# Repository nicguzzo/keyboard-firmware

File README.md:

firmware for 2 pieces ergonomic mechanical keyboard

pacman -S arm-none-eabi-gcc arm-none-eabi-gdb arm-none-eabi-binutils arm-none-eabi-newlib

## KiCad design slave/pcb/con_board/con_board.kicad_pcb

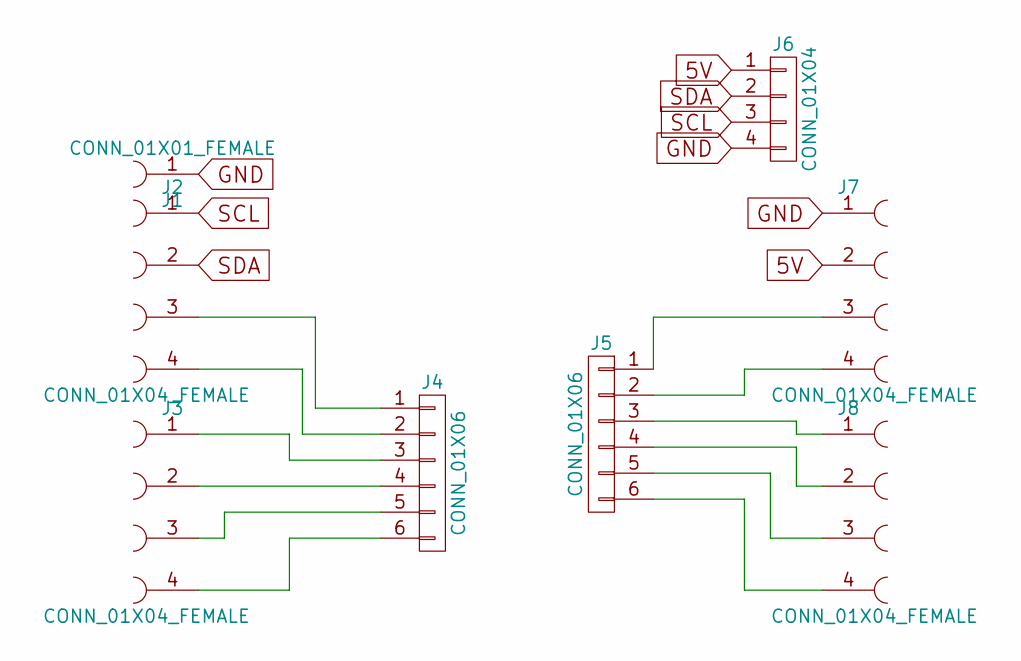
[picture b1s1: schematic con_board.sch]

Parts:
J1: CONN_01X01_FEMALE; Pin_Header_Straight_1x01_Pitch2.54mm
J2, J3, J7, J8: CONN_01X04_FEMALE; Pin_Header_Straight_1x04_Pitch2.54mm
J4, J5: CONN_01X06; Pin_Header_Straight_1x06_Pitch2.54mm
J6: CONN_01X04; Pin_Header_Straight_1x04_Pitch2.54mm

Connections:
5V: J6.1, J7.2
GND: J1.1, J6.4, J7.1
unnamed: J2.3, J4.1
unnamed: J2.4, J4.2
unnamed: J3.1, J4.3
unnamed: J3.2, J4.4
unnamed: J3.3, J4.5
unnamed: J3.4, J4.6
unnamed: J5.1, J7.3
unnamed: J5.2, J7.4
unnamed: J5.3, J8.1
unnamed: J5.4, J8.2
unnamed: J5.5, J8.3
unnamed: J5.6, J8.4
SCL: J2.1, J6.3
SDA: J2.2, J6.2

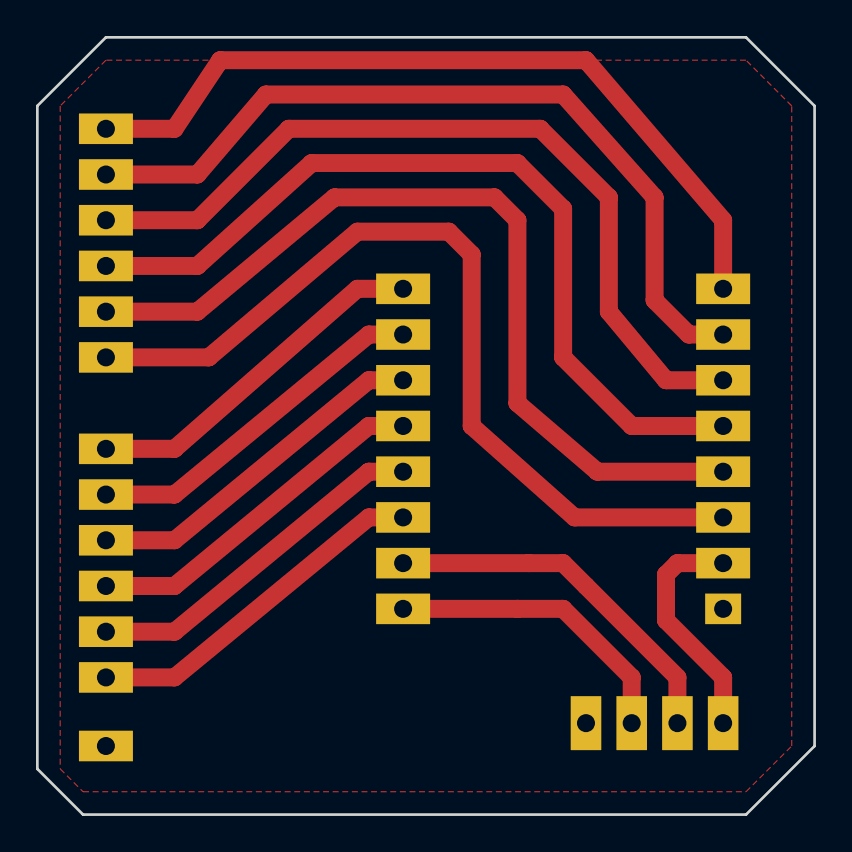
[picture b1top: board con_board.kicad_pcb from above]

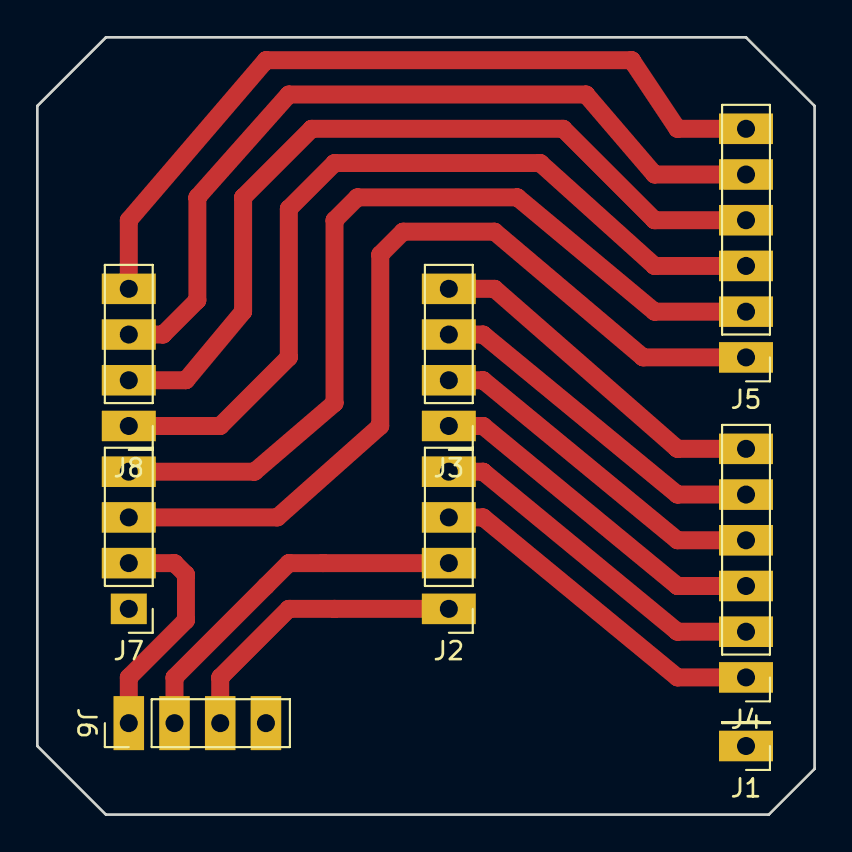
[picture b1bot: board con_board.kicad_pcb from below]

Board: 2 copper layers, 43.2 x 43.2 mm, 8 parts (8 on the bottom side), 16 nets.

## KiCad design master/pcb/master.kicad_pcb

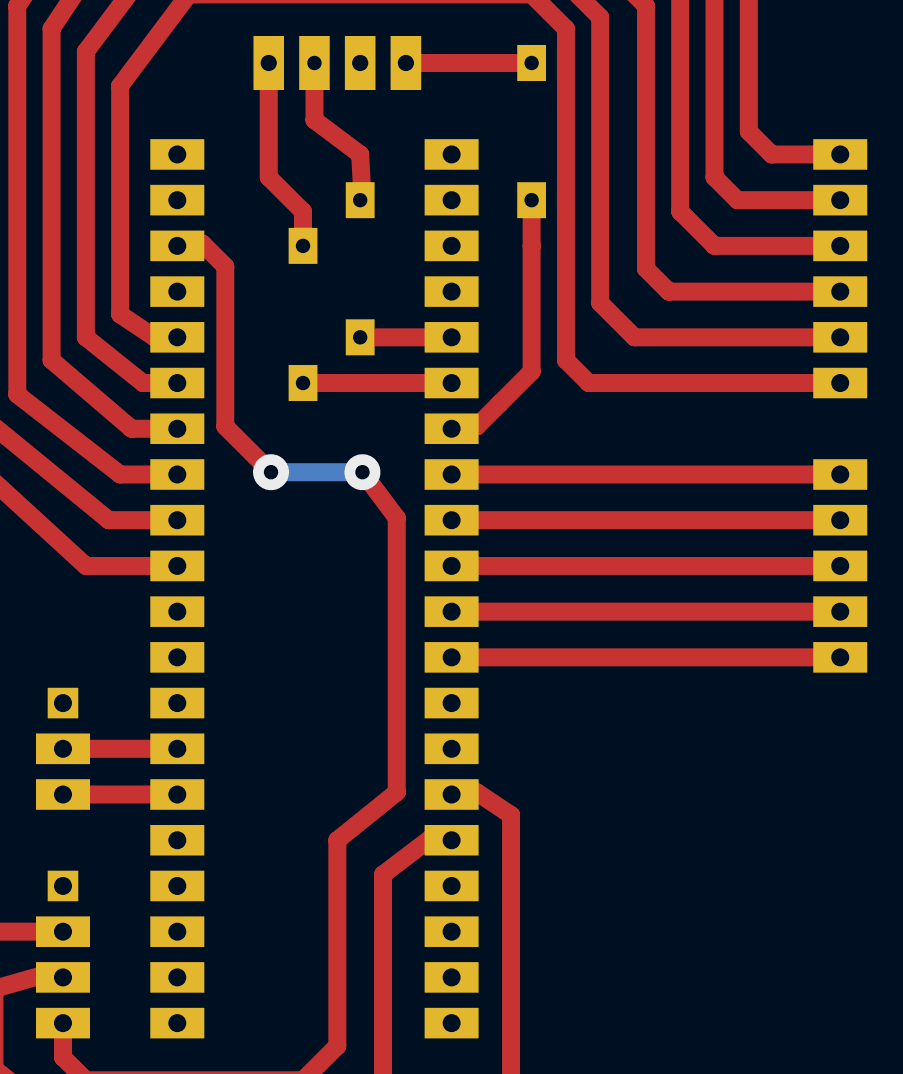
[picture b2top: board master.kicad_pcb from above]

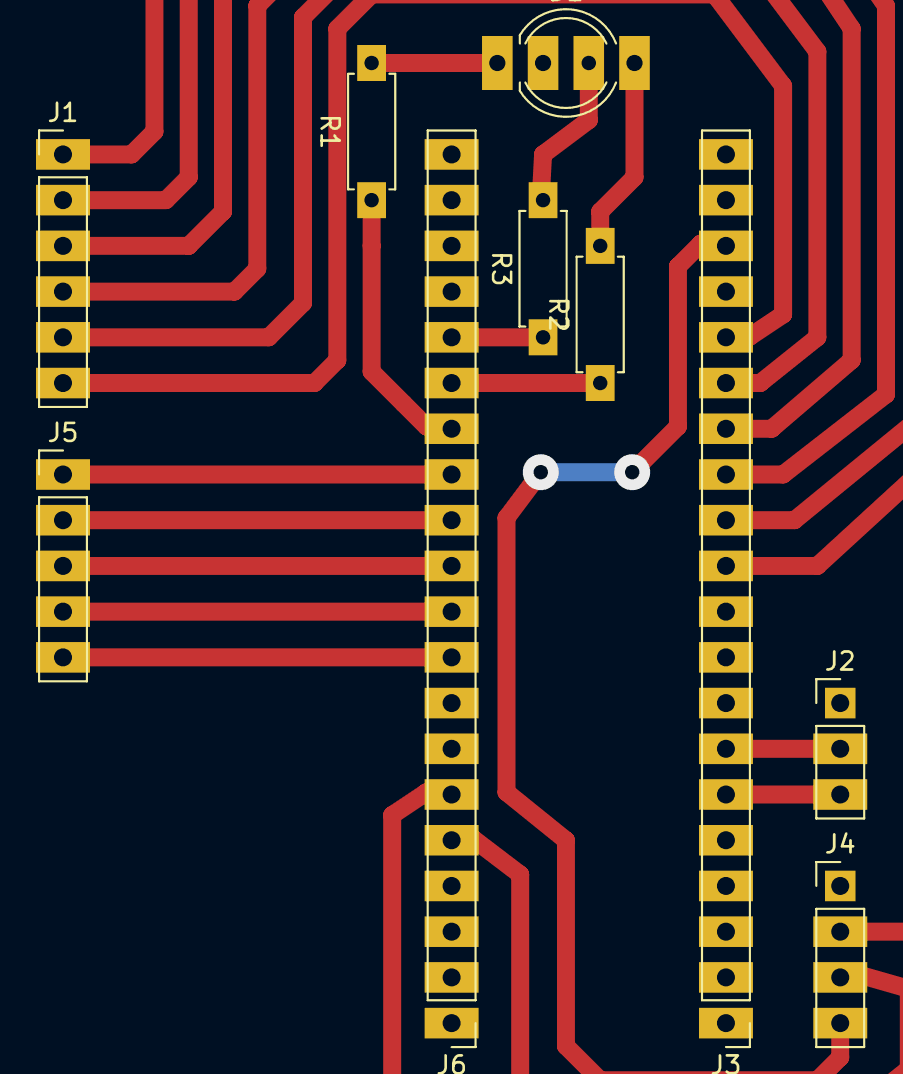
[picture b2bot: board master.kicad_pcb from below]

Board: 2 copper layers, 10 parts (10 on the bottom side), 23 nets.

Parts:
D1: LED_RCBG; LED_D5.0mm-4
J1: CONN_01X06; Pin_Header_Straight_1x06_Pitch2.54mm
J2: CONN_01X03; Pin_Header_Straight_1x03_Pitch2.54mm
J3, J6: CONN_01X20; Pin_Header_Straight_1x20_Pitch2.54mm
J4: CONN_01X04; Pin_Header_Straight_1x04_Pitch2.54mm
J5: CONN_01X05; Pin_Header_Straight_1x05_Pitch2.54mm
R1, R2, R3: R_Small; R_Axial_DIN0207_L6.3mm_D2.5mm_P7.62mm_Horizontal

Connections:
+5V: J3.18, J4.4
GND: D1.2, J2.1, J3.19, J4.1
unnamed: D1.1, R1.2
unnamed: D1.3, R3.2
unnamed: D1.4, R2.2
unnamed: J1.1, J3.11
unnamed: J1.2, J3.12
unnamed: J1.3, J3.13
unnamed: J1.4, J3.14
unnamed: J1.5, J3.15
unnamed: J1.6, J3.16
unnamed: J2.2, J3.7
unnamed: J2.3, J3.6
unnamed: J4.2, J6.6
unnamed: J4.3, J6.5
unnamed: J5.1, J6.13
unnamed: J5.2, J6.12
unnamed: J5.3, J6.11
unnamed: J5.4, J6.10
unnamed: J5.5, J6.9
unnamed: J6.14, R1.1
unnamed: J6.15, R2.1
unnamed: J6.16, R3.1

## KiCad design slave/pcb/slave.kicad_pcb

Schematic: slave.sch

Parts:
C1: C_Small; C_Disc_D3.4mm_W2.1mm_P2.50mm
D1, D2, D3: LED; LED_D3.0mm
J1: row; Pin_Header_Straight_1x06_Pitch2.54mm
J2: col; Pin_Header_Straight_1x06_Pitch2.54mm
J3: i2c_conn; Pin_Header_Straight_1x02_Pitch2.54mm
J4: power_conn; Pin_Header_Straight_1x02_Pitch2.54mm
R1: 10k; R_Axial_DIN0207_L6.3mm_D2.5mm_P7.62mm_Horizontal
R2, R5, R6: 1k; R_Axial_DIN0207_L6.3mm_D2.5mm_P7.62mm_Horizontal
R3, R4: 4.7k; R_Axial_DIN0207_L6.3mm_D2.5mm_P7.62mm_Horizontal
U1: ATTINY2313A-PU; DIP-20_W7.62mm

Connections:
+5V: C1.1, J4.1, R1.1, R3.1, R4.1, U1.20 (VCC)
GND: C1.2, D1.1 (K), D2.1 (K), D3.1 (K), J4.2, U1.10 (GND)
unnamed: D1.2 (A), R2.2
unnamed: D2.2 (A), R5.2
unnamed: D3.2 (A), R6.2
unnamed: J1.1, U1.12 ((PCINT0/AIN0)PB0)
unnamed: J1.2, U1.13 ((PCINT1/AIN1)PB1)
unnamed: J1.3, U1.14 ((PCINT2/OC0A)PB2)
unnamed: J1.4, U1.15 ((PCINT3/OC1A)PB3)
unnamed: J1.5, U1.16 ((PCINT4/OC1B)PB4)
unnamed: J1.6, U1.18 ((PCINT6/MISO/DO)PB6)
unnamed: J2.1, U1.2 ((PCINT11/RXD)PD0)
unnamed: J2.2, U1.3 ((PCINT12/TXD)PD1)
unnamed: J2.3, U1.6 ((PCINT13/CKOUT/XCK/INT0)PD2)
unnamed: J2.4, U1.7 ((PCINT14/INT1)PD3)
unnamed: J2.5, U1.8 ((PCINT15/T0)PD4)
unnamed: J2.6, U1.9 ((PCINT16/OC0B/T1)PD5)
unnamed: J3.1, R4.2, U1.17 ((PCINT5/MOSI/DI/SDA)PB5)
unnamed: J3.2, R3.2, U1.19 ((PCINT7/USCK/SCK/SCL)PB7)
unnamed: R1.2, U1.1 (PA2(~RESET~/dW/PCINT10))
unnamed: R2.1, U1.11 ((PCINT17/ICP1)PD6)
unnamed: R5.1, U1.4 (PA1(XTAL2/PCINT9))
unnamed: R6.1, U1.5 (PA0(XTAL1/CLKI/PCINT8))

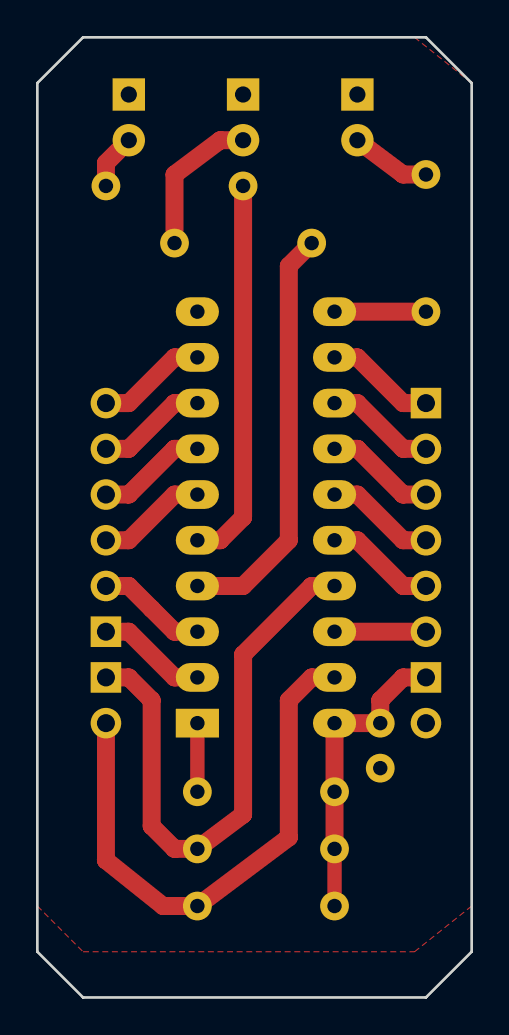
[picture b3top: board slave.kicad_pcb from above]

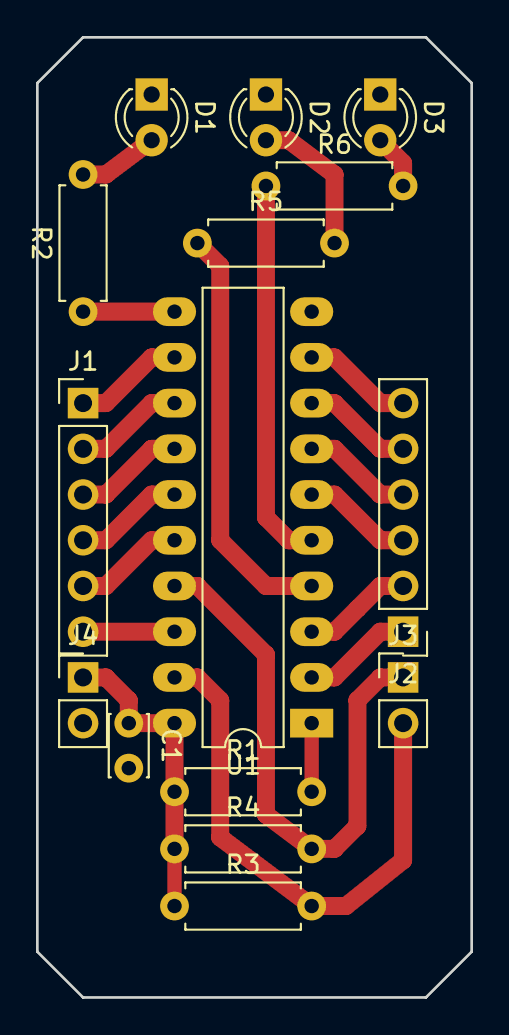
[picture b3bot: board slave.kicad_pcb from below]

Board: 2 copper layers, 24.1 x 53.3 mm, 15 parts (15 on the bottom side), 23 nets.

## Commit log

2017-07-18 attiny2313
2017-07-22 i2c and usb working, mouse example only
2017-07-22 TODO: improve README
2017-07-23 composite usb working, hid(mouse/keyboard) + serial
2017-07-25 slave pcb
2017-07-25 conn_board
2017-07-25 removed cache.lib file
2017-07-25 ignore cache.lib
2017-08-05 completed keyscan master/slave
2017-08-05 master pcb
2017-08-05 usb stuff from C++ to C
2017-08-05 master pcb layout change
2017-08-06 initial layers implementation
2017-08-06 layers...
2017-08-06 layers ...
2017-08-12 save conf to flash
2017-09-19 spacebar bug fixed, i2c detection improved (ST basecode bug)
2018-02-15 dfu loader
2018-02-15 files
2018-02-18 pbc modifications
2018-02-19 layers... work in progress
2018-02-19 ignore swp files
2018-02-19 basic mouse movement, bootloader fixes
2018-03-02 cmd arrows and mouse
2018-03-05 mouse working con cmd layer
2018-03-05 fixed saving of layer struct, added padding in layer_t , mouse working
2018-03-05 using square increment
2018-03-06 mouse buttons, other bugfixes
2018-03-07 fix bug when switching layer before key release
2022-09-19 fix cdc descriptor
2022-09-19 utils submodule
